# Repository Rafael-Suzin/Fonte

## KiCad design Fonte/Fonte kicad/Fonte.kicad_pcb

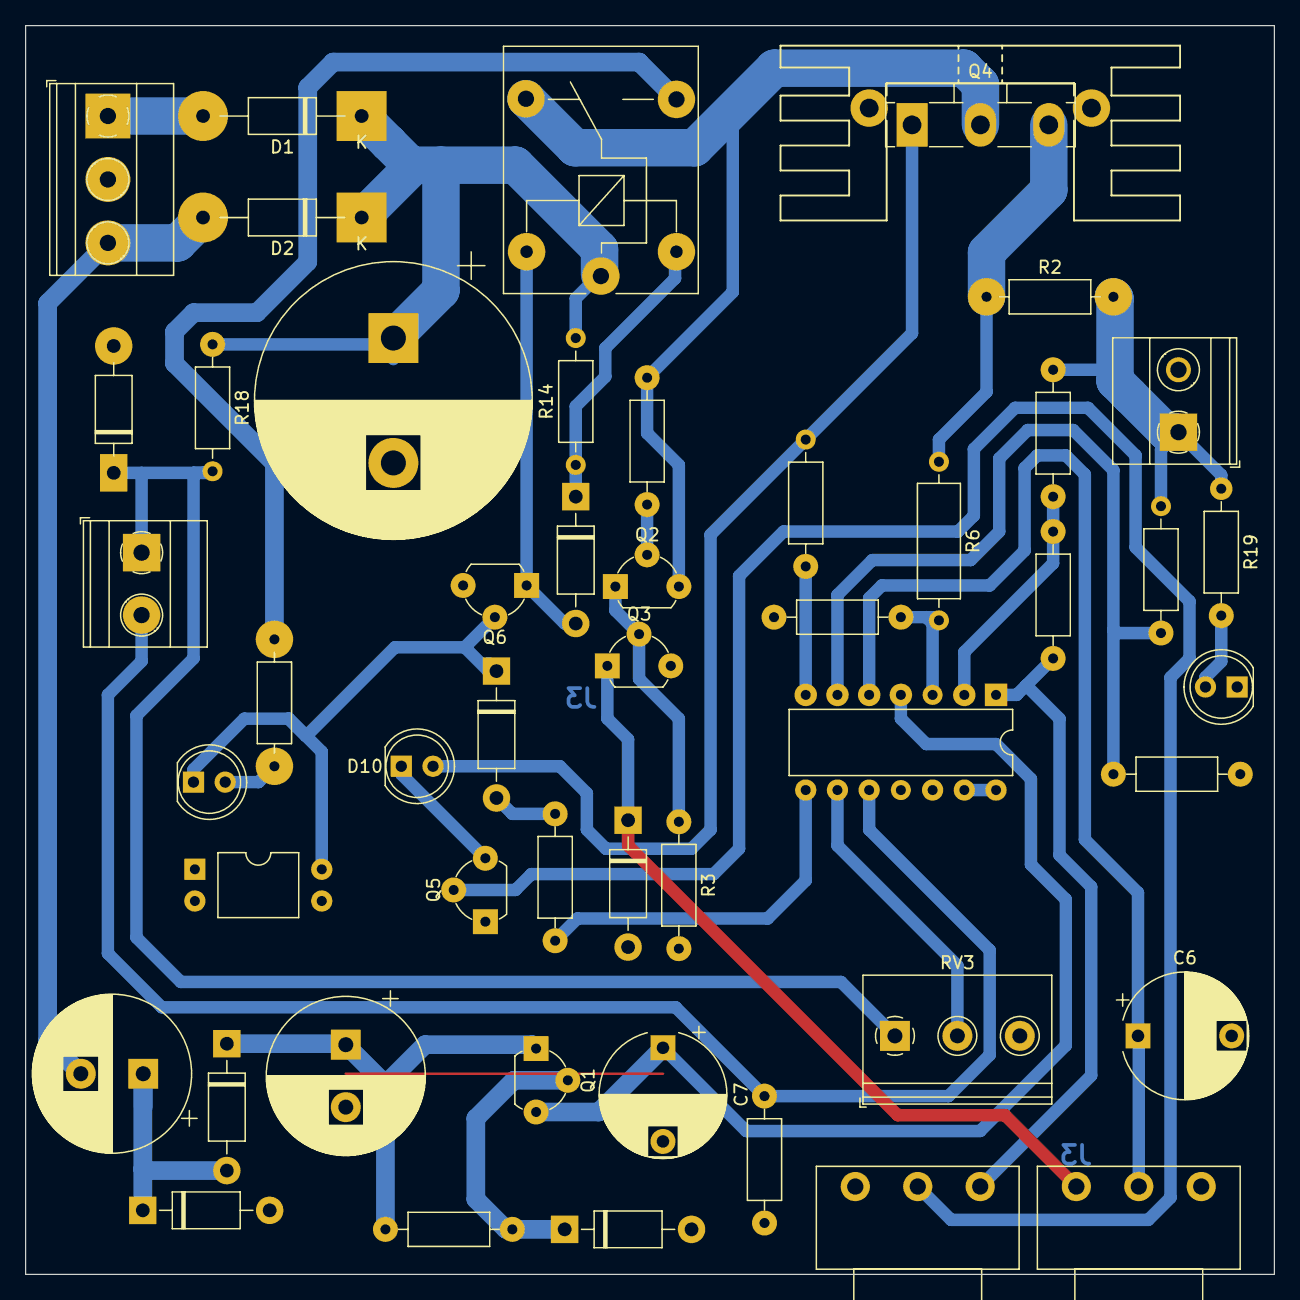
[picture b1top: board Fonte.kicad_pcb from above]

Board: 2 copper layers, 100.0 x 100.0 mm, 50 parts (0 on the bottom side), 35 nets.

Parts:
C1: C_Polarized; CP_Radial_D22.0mm_P10.00mm_SnapIn
C2, C3: 330u; CP_Radial_D12.5mm_P5.00mm
C6: 10u; CP_Radial_D10.0mm_P7.50mm
C7: 100n; CP_Radial_D10.0mm_P7.50mm
D1, D2: 1N4007; D_DO-41_SOD81_P12.70mm_Horizontal
D3, D4, D7, D8: 1N4007; D_DO-41_SOD81_P10.16mm_Horizontal
D5: D_Zener; D_DO-41_SOD81_P10.16mm_Horizontal
D6, D9: 1N53xxB; D_DO-41_SOD81_P10.16mm_Horizontal
D10, D11, D12: LED; LED_D5.0mm
HS1: Heatsink; Heatsink_Stonecold_HS-132_32x14mm_2xFixation1.5mm
J1: Screw_Terminal_01x03; TerminalBlock_Phoenix_MKDS-1,5-3-5.08_1x03_P5.08mm_Horizont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
J2: Conn_02x02_Top_Bottom; DIP-4_W10.16mm
J3, J4: Screw_Terminal_01x02; TerminalBlock_Phoenix_MKDS-1,5-2_1x02_P5.00mm_Horizontal
K1: SANYOU_SRD_Form_C; Relay_SPDT_SANYOU_SRD_Series_Form_C
Q1, Q6: BC547; TO-92L_Wide
Q2, Q3: BC556; TO-92L_Wide
Q4: IRF540N; TO-218-3_Vertical
Q5: 2N7000; TO-92L_Wide
R1: 1k; R_Axial_DIN0207_L6.3mm_D2.5mm_P10.16mm_Horizontal
R2: R_Small; R_Axial_DIN0207_L6.3mm_D2.5mm_P10.16mm_Horizontal
R3, R4, R5, R7, R8, R9, R11, R12, R13, R16, R18, R19, R20: R; R_Axial_DIN0207_L6.3mm_D2.5mm_P10.16mm_Horizontal
R6: R; R_Axial_DIN0309_L9.0mm_D3.2mm_P12.70mm_Horizontal
R14: 100; R_Axial_DIN0207_L6.3mm_D2.5mm_P10.16mm_Horizontal
RV1, RV2: R_Potentiometer; Potentiometer_Piher_PC-16_Single_Horizontal
RV3: R_Potentiometer; TerminalBlock_Philmore_TB133_1x03_P5.00mm_Horizontal
U1: LM324; DIP-14_W7.62mm

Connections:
/V_Led_G: D12.2 (A), R19.2
/V_Led_Lrg: D10.2 (A), Q4.1 (G), R11.2
/V_Led_Red: D11.2 (A), R4.2
/V_Ref_T: D9.1 (K), J4.1, R18.2, RV3.1
/V_Vmax: C6.1, RV1.2, U1.5 (+)
/V_Vmax-: R12.2, R20.1, U1.6 (-)
/V_dif_op: R9.2, RV2.3, U1.1
/V_in+: D1.2 (A), J1.1
/V_in-: C2.2, D2.2 (A), J1.3
/V_max_A: Q5.2 (G), RV2.2
/V_max_T: RV3.2, U1.9 (-)
/V_op_T: R16.1, U1.8
/V_out: J3.1, R2.2, R7.1, R12.1, R19.1
/V_ref_VCC: D5.1 (K), Q1.2 (B), R1.2
/V_shant: Q4.3 (S), R2.1, R6.1
GND: C1.2, C3.2, C6.2, C7.2, D4.2 (A), D5.2 (A), D6.2 (A), D9.2 (A), D12.1 (K), J1.2, J2.2, J3.2, Q5.1 (S), Q6.3 (E), R3.2, R8.2, R13.2, R20.2, RV1.3, RV2.1, RV3.3, U1.11 (V-), U1.12 (+)
NO: K1.3, R4.1
unnamed: C2.1, D3.2 (A), D4.1 (K)
unnamed: C3.1, D3.1 (K), Q1.1 (C), R1.1
unnamed: D7.2 (A), K1.5, Q6.1 (C)
unnamed: D7.1 (K), K1.2, R14.1
unnamed: D8.2 (A), R16.2
unnamed: D10.1 (K), Q5.3 (D)
unnamed: D8.1 (K), D11.1 (K), J2.4, Q6.2 (B)
unnamed: Q2.2 (B), Q3.3 (E), R5.2
unnamed: Q2.1 (C), Q3.2 (B), R3.1
unnamed: K1.4, Q2.3 (E), Q4.2 (D), R5.1
unnamed: R11.1, U1.7
unnamed: R6.2, R8.1, U1.3 (+)
unnamed: R7.2, R9.1, U1.2 (-)
unnamed: U1.13 (-), U1.14
VCC: C7.1, Q1.3 (E), U1.4 (V+)
V_ntc: J4.2, R13.1, U1.10 (+)
V_ref: D6.1 (K), Q3.1 (C), RV1.1
V_ret: C1.1, D1.1 (K), D2.1 (K), K1.1, R14.2, R18.1
